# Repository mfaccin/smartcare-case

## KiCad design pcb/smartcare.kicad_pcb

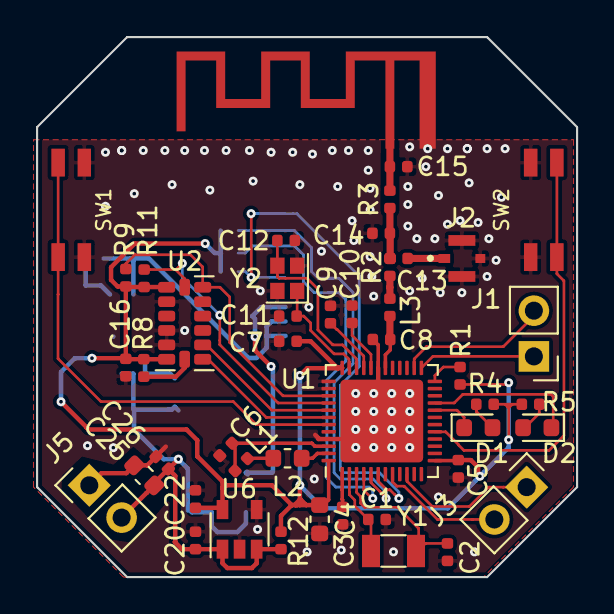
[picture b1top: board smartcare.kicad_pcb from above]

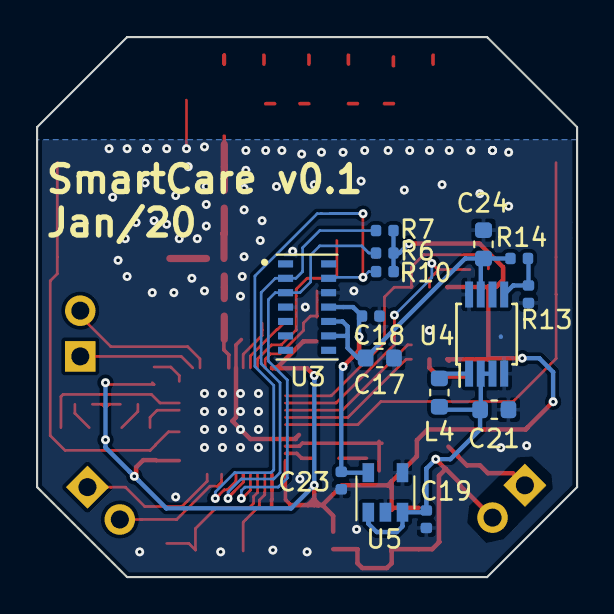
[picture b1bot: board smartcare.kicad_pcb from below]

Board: 2 copper layers, 30.0 x 30.0 mm, 61 parts (15 on the bottom side), 40 nets.

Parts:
AE1: AN043
C1, C2, C11, C12: 12pF; C_0402_1005Metric
C3, C5, C7, C16, C18, C26: 100nF; C_0402_1005Metric
C4: 4.7uF; C_0603_1608Metric
C6, C19, C20, C22: 1uF; C_0402_1005Metric
C8: 0.8pF; C_0402_1005Metric
C9: 100pF; C_0402_1005Metric
C10, C13, C14, C15: NC; C_0402_1005Metric
C17, C21: 10uF; C_0603_1608Metric
C23: 2.2uF; C_0402_1005Metric
C24: 22uF; C_0603_1608Metric
C25: 47uF; C_0603_1608Metric
D1: RED; LED_0603_1608Metric
D2: GREEN; LED_0603_1608Metric
J1, J3, J5: Conn_01x02; PinHeader_1x02_P2.54mm_Vertical
J2: Conn_Coaxial; IPEX_20369-001E-03
L1: 15nH; L_0402_1005Metric
L2: 10uH; L_0603_1608Metric
L3: 3.9nH; L_0402_1005Metric
L4: 2.2uH; L_0603_1608Metric
R1, R12: NC; R_0402_1005Metric
R2, R3: 0; R_0402_1005Metric
R4, R5: 220; R_0402_1005Metric
R6, R7, R8, R9, R10, R11: 4.7k; R_0402_1005Metric
R13: 100k; R_0402_1005Metric
R14: 750k; R_0402_1005Metric
SW1, SW2: SW_Push; EVQPUA
U1: nRF52832-QFxx; QFN-48-1EP_6x6mm_P0.4mm_EP4.6x4.6mm
U2: ADXL345; LGA-14_3x5mm_P0.8mm_LayoutBorder1x6y
U3: MAX30101EFD; OLGA-14
U4: PAM2401; MSOP-8_3x3mm_P0.65mm
U5: TPS78318; SOT-23-5
U6: TPS78223; SOT-23-5
Y1: 32.768kHz; Crystal_SMD_3215-2Pin_3.2x1.5mm
Y2: 32MHz; Crystal_SMD_2016-4Pin_2.0x1.6mm

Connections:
/microcontroller/ACCEL_INT1: U1.42, U2.8
/microcontroller/ACCEL_INT2: U1.41, U2.9
/microcontroller/ACCEL_SCL: R11.2, U1.40, U2.14
/microcontroller/ACCEL_SDA: R9.2, U1.39, U2.13
/microcontroller/BUTTON1: SW1.2, U1.43
/microcontroller/BUTTON2: SW2.2, U1.17
/microcontroller/HEART_RATE_INT: R10.2, U1.6, U3.13
/microcontroller/HEART_RATE_SCL: R7.2, U1.5, U3.2
/microcontroller/HEART_RATE_SDA: R6.2, U1.4, U3.3
/microcontroller/LED_GREEN: D2.1, U1.21
/microcontroller/LED_RED: D1.1, U1.20
/microcontroller/RESET: R1.2, U1.24
/microcontroller/RX: J3.2, U1.8
/microcontroller/SWDCLK: J1.1, U1.25
/microcontroller/SWDIO: J1.2, U1.26
/microcontroller/TX: J3.1, U1.10
/microcontroller/VDD: C4.1, C5.1, C7.1, C16.1, C22.1, R1.1, R4.1, R5.1, R6.1, R7.1, R8.1, R9.1, R10.1, R11.1, R12.1, U1.13, U1.36, U1.48, U2.1, U2.6, U6.5
/peripherals/+1V8: C18.1, C23.1, U3.11, U5.5
/peripherals/+5V: C17.1, C24.1, R14.1, U3.9, U3.10, U4.7
/power_supply/VBAT: C19.1, C20.1, C21.1, C25.1, C26.1, J5.2, L4.1, R12.2, U4.2, U4.3, U5.1, U5.3, U6.1, U6.3
GND: AE1.1, C1.2, C2.2, C3.2, C4.2, C5.2, C6.2, C7.2, C8.2, C9.1, C10.1, C11.1, C12.1, C14.2, C15.1, C15.2, C16.2, C17.2, C18.2, C19.2, C20.2, C21.2, C22.2, C23.2, C24.2, C25.2, C26.2, J2.2, J5.1, R3.2, R13.2, SW1.1, SW2.1, U1.31, U1.37, U1.38, U1.45, U1.49, U2.2, U2.4, U2.5, U3.4, U3.12, U4.4, U4.8, U5.2, U5.4, U6.2, U6.4, Y2.2, Y2.4
unnamed: C1.1, U1.2, Y1.1
unnamed: C2.1, U1.3, Y1.2
unnamed: C3.1, U1.1
unnamed: C6.1, L1.1, U1.46
unnamed: C8.1, L3.1, U1.30
unnamed: C9.2, U1.33
unnamed: C10.2, U1.32
unnamed: C11.2, U1.35, Y2.1
unnamed: C12.2, U1.34, Y2.3
unnamed: C13.1, C14.1, R2.2, R3.1
unnamed: C13.2, J2.1
unnamed: D1.2, R4.2
unnamed: D2.2, R5.2
unnamed: L1.2, L2.1
unnamed: L2.2, U1.47
unnamed: L3.2, R2.1
unnamed: L4.2, U4.1
unnamed: R8.2, U2.7
unnamed: R13.1, R14.2, U4.5

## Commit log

2020-01-13 First commit.
2020-01-14 Modify pin headers to do not export the 3D model.
2020-01-14 Base sketches started.
2020-01-16 Add first sketches.
2020-01-16 Band first version.
2020-01-17 First assembly drawing.
2020-01-17 Fix design and add some chamfers make more usable
2020-01-17 Add some colors
2020-01-17 Update and organize the assembly
2020-01-17 Fix design and clean it up
2020-01-17 Add a nice color
2020-01-17 Update parts and add PCB
2020-01-17 Fix model error
2020-01-17 Refresh models
